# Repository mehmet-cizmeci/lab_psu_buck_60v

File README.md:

# Lab güç kaynağı buck modülü — 0,8–60 V / 0–10 A

TL494 denetleyicili, IR2101 üst kapı sürücülü, asenkron (diyotlu) **buck** dönüştürücü kartı.
Laboratuvar güç kaynağının güç katı olarak tasarlandı: ön paneldeki iki pot ile **gerilim (CV)** ve **akım (CC)** ayarlanır.
İki kanallı bir kaynak için aynı karttan iki adet kullanılabilir.

| | |
|---|---|
| Giriş | 12–70 V DC (60 V çıkış için giriş ≥ 68 V) |
| Çıkış | 0,8–60 V (CV), 0–10 A (CC); en fazla ≈ 300 W |
| Yardımcı besleme | harici +12 V (denetleyici, sürücü, fan) ve +5 V (panel ölçeri) |
| Anahtarlama | ≈ 80 kHz, IRF3710 üst anahtar, MBR20200CT serbest diyot |
| Akım ölçme | 10 mΩ şönt + LM2904, IMON çıkışı 0,2 V/A |
| Kart | 120 × 55 mm, **tek katman** (alt yüz bakır), 1,6 mm FR4 |
| Tasarım | KiCad 10 — şema, kart, kütüphaneler, Gerber ve BOM bu depoda |

## Devre
- **Kontrol:** TL494'ün iki hata yükselteci kullanılır: biri gerilim (CV), biri akım (CC) döngüsü. Tek uçlu mod (pin 13 = GND).
- **Kapı sürücü:** IR2101 yalnız üst çıkışıyla (HO) kullanılır; BCP56/BCP53 emitör izleyici tampon kapıyı ≈ 1 A tepe akımla sürer.
- **Bobin (L1):** iki adet KT130-26 toroid nüve üst üste, 26 tur, 2 × 1,0 mm emaye tel paralel (10 A altında ≈ 75 µH; sardıktan sonra ölçün).
- **Korumalar:**
  - giriş sigortası F1 (6,3 A gecikmeli) ve tek yönlü TVS D12: giriş ters bağlanırsa TVS iletir, F1 atar;
  - çıkış sigortası F2 (10 A) ve ters diyot D4: çıkışa ters akü bağlanırsa F2 atar;
  - hızlı aşırı akım kesmesi (≈ 12 A, karşılaştırıcı → DTC), yumuşak başlatma;
  - pot telleri koparsa ayar 0'a düşer (çıkış kapanır);
  - soğutucuya NC termostat girişi (J9).
- Asenkron yapı çıkıştan girişe akım basmaz; akü veya kondansatör bağlı çıkışta güvenlidir.
- Çıkış eksisi (OUT−) şönt üzerinden geçtiği için **şaseye bağlanmaz**; kanallar seri bağlanmaz.

Şemanın PDF'i: [uretim/lab_psu_buck_60v_sema.pdf](uretim/lab_psu_buck_60v_sema.pdf)

## Bağlantılar
| Konnektör | Pinler |
|---|---|
| J3 GİRİŞ 12–70 V | 1 = +, 2 = GND |
| J2 ÇIKIŞ 0–60 V | 1 = +, 2 = − |
| J1 yardımcı besleme | 1 = GND, 2 = +5 V, 3 = +12 V |
| J7 V POT, J8 I POT | 10 kΩ lineer pot; 3 ve 4 numaralı pinler pot GND ucuna **ayrı tellerle** (kopma algılama) |
| J9 TERMOSTAT | NC termostat (70 °C); kullanılmıyorsa köprüleyin |
| J10 IMON | 0,2 V/A akım çıkışı (panel ölçeri veya mikrodenetleyici) |
| J11 METRE | panel volt/ampermetresi: 1 = +5 V, 2 = ÇIKIŞ−, 3 = ÇIKIŞ+ |
| J12 FAN | 12 V fan |

## Kart ve montaj

- Bakır yalnız **alt yüzde**; evde (toner/lazer) veya tek katman sipariş olarak üretilebilir. SMD parçalar alt yüzde, THT parçalar üst yüzde.
- Üst yüzdeki (F.Cu) yollar ve vialar **tel atlamalarını** gösterir; Gerber'e F.Cu basılmaz:
  - 5 kalın GND teli (1,5 mm delik): ≈ 17, 22, 27, 26 ve 7 mm,
  - 4 ince sinyal teli (0,5 mm delik): SW ≈ 10 mm, VPOT_K ≈ 12 mm, DTC ≈ 20 mm, FB ≈ 12 mm.
- 0 Ω köprüler (R1, R37–R39 1206; R20, R21, R41 2512) SMD bölgesindeki yol geçişleridir.
- Q1 (IRF3710) ve D2 (MBR20200CT) kartın **altında yatık** durur; bacaklar 90° bükülür, sekmeler silikon ped + plastik burçla
  kart boyutundaki alüminyum plakaya bağlanır (sekmeler farklı potansiyelde, mutlaka izole edin). Plakanın üstüne SMD bölgesi için yalıtkan levha koyun.
- Güç yollarının maskesi açıktır; lehim ve bakır telle takviye edilebilir.

## Üretim dosyaları (`uretim/`)
| Dosya | İçerik |
|---|---|
| `lab_psu_buck_60v_gerber.zip` | Gerber (B.Cu, B.Mask, B.Paste, F/B.Silkscreen, Edge.Cuts) + delik dosyası |
| `gerber/` | aynı dosyalar açık hâlde |
| `BOM.csv` | malzeme listesi: üretici parça numarası, **Özdisan** ve **LCSC** stok kodları (`;` ayraçlı) |
| `BOM_JLCPCB.csv`, `CPL_JLCPCB.csv` | montajlı sipariş için LCSC kodlu BOM ve parça konum dosyası |
| `konum_alt_kicad.csv` | KiCad konum dosyası (alt yüz SMD) |
| `lab_psu_buck_60v_sema.pdf` | şema |

Stok kodları örnek olarak verilmiştir (Kasım 2026); sipariş öncesi stok ve fiyatı tedarikçiden kontrol edin.
Bazı Özdisan kodları stok durumuna göre seçilmiş **eşdeğer/muadil** parçalardır, `BOM.csv` "Not" sütununda belirtilmiştir:
- 1 µF 100 V kondansatörler (C5, C6, C7, C12, C13, C14, C33) için 0805 kılıf muadil: 1206 pedine ortalanarak lehimlenir.
- D12 için SMCJ100A (tek yönlü, aynı SMC kılıf). SMCJ85A bulunabiliyorsa o tercih edilir.
- 5×20 cam sigortaların **DC** anma değerini (≥ 80 V DC) veri sayfasından kontrol edin.

**Örnek maliyet (Kasım 2026, KDV ve kargo hariç):** kart üzerindeki malzemeler 1 kart için ≈ 12 USD,
10 kartlık alımda kart başına ≈ 8 USD. PCB, soğutucu, pot, panel ölçeri ve kasa hariçtir.

## KiCad
- KiCad 10 ile `lab_psu_buck_60v.kicad_pro` dosyasını açın.
- Karta özel semboller, footprint'ler ve 3D modeller `kutuphane/` altındadır (`lab_buck`); proje kütüphane tablosu bunları otomatik bulur.
  Diğer parçalar KiCad'in standart kütüphanelerindendir.
- Tasarım kuralları `lab_psu_buck_60v.kicad_dru` içindedir (hat ≥ 0,5 mm, dolgu–yol 1 mm, üst yüzde dolgu yok).
- DRC 0, ERC 0, şema–kart uyumu tam (Rev 0.4).

## İlk çalıştırma ve uyarılar
- Kartta **70 V DC'ye kadar** gerilim ve yüksek akım vardır. İlk denemeyi akım sınırlı bir kaynakla, düşük giriş geriliminde yapın.
- Önce yardımcı beslemeyi (+12 V) verip TL494 osilatörünü ve kapı sinyalini kontrol edin, sonra ana girişi yavaşça yükseltin.
- Kompanzasyon değerleri başlangıç değerleridir; tezgâhta yük basamağı ile doğrulanmalıdır. L1 endüktansını DC öngerilim altında ölçün.
- Q1 ve D2 soğutucusuz çalıştırılmamalıdır.

## Sürüm
**Rev 0.4** (Kasım 2026)

## Lisans
Bu donanım tasarımı **CERN Open Hardware Licence Version 2 – Permissive (CERN-OHL-P v2)** ile lisanslanmıştır, bkz. [LICENSE](LICENSE).

İzan Mekatronik — https://www.izanmekatronik.com.tr

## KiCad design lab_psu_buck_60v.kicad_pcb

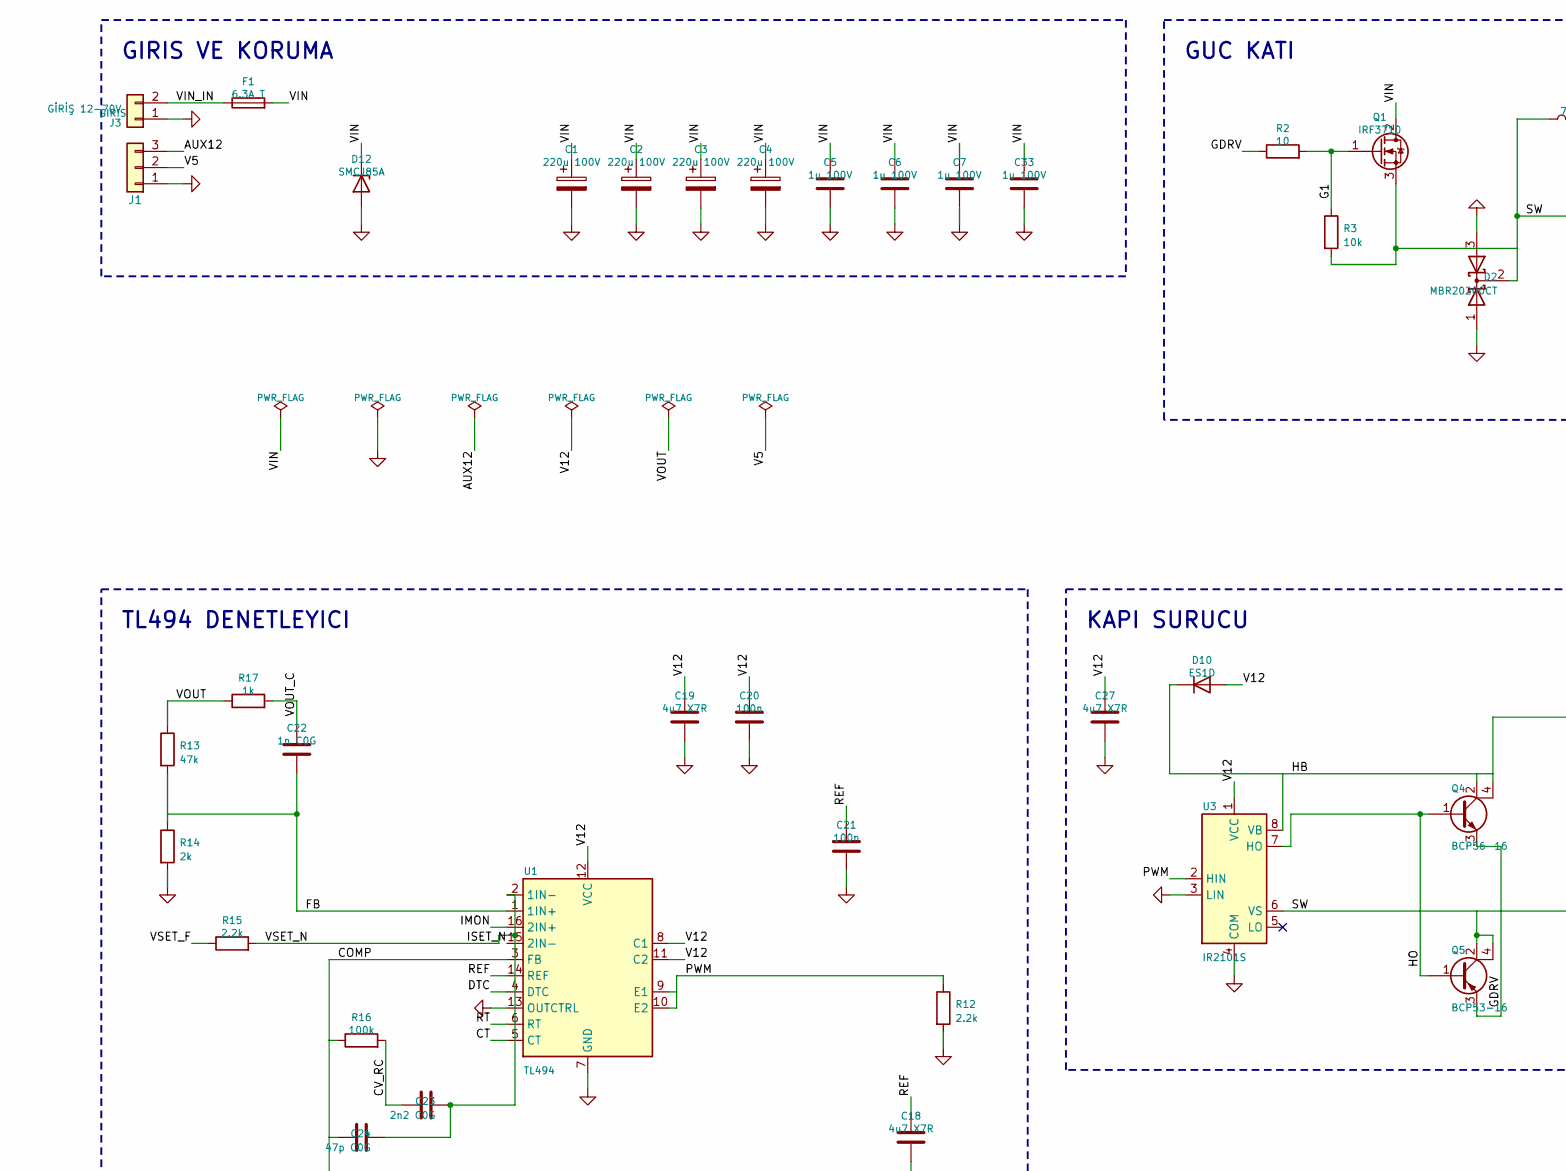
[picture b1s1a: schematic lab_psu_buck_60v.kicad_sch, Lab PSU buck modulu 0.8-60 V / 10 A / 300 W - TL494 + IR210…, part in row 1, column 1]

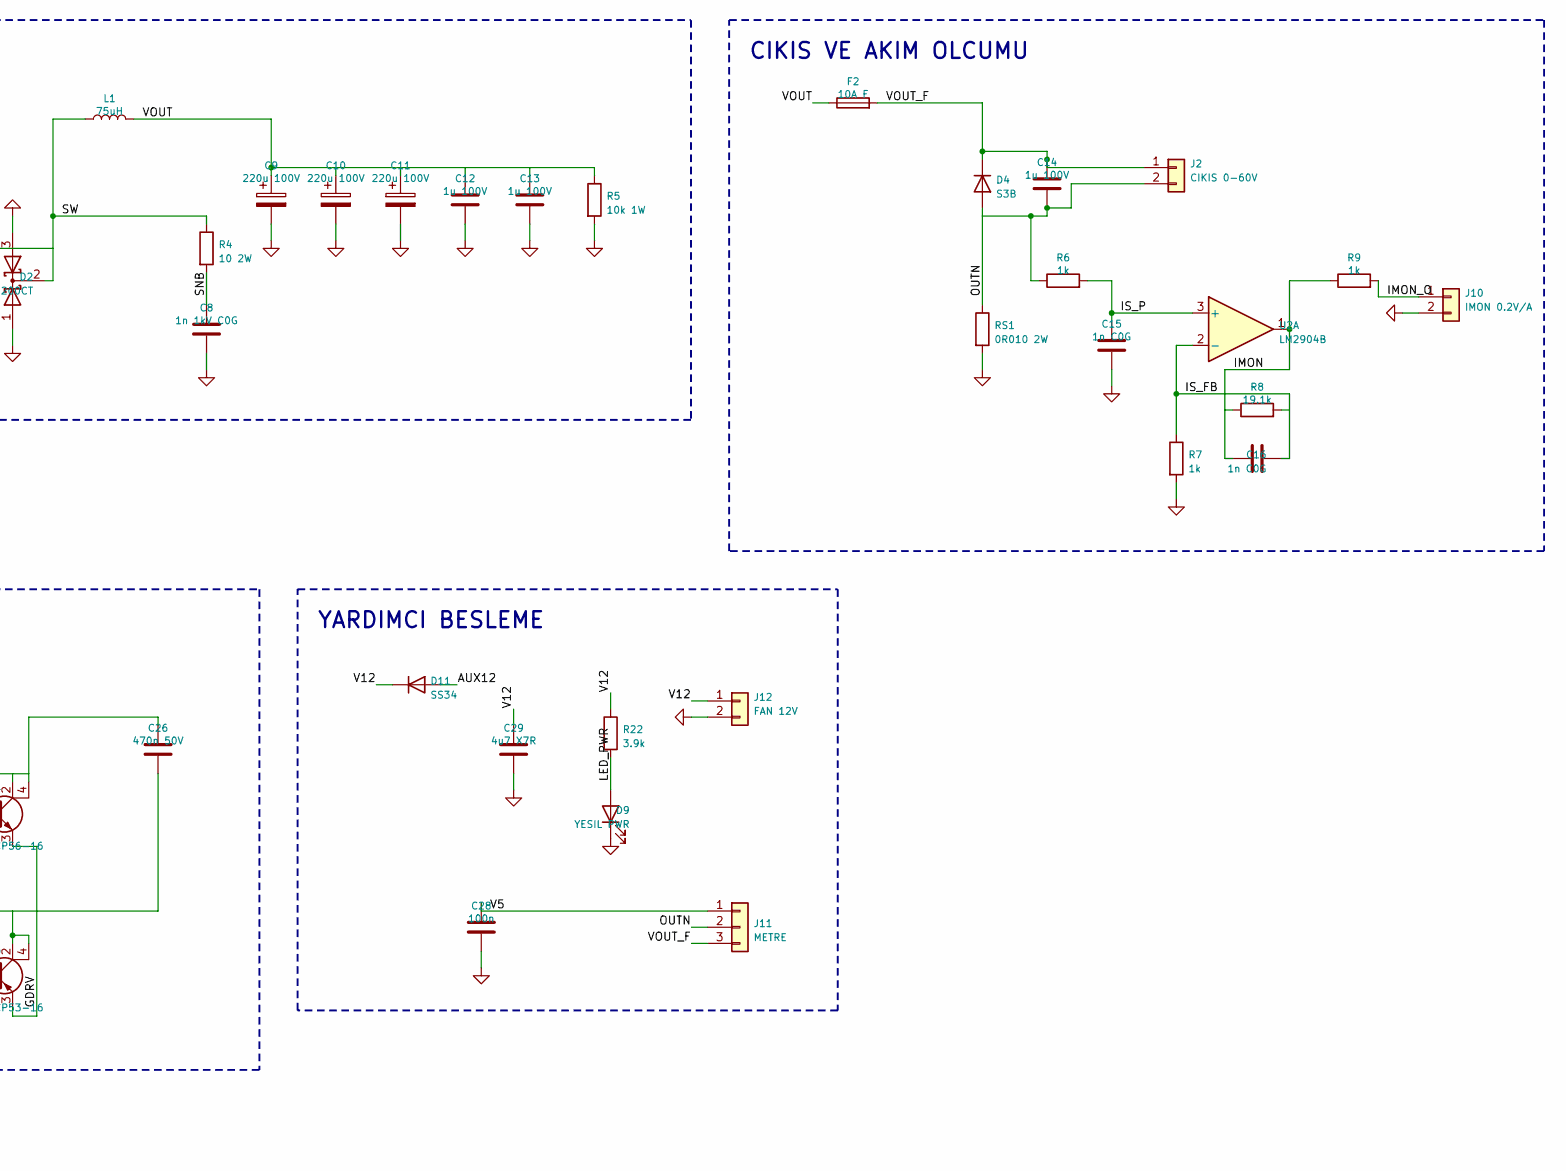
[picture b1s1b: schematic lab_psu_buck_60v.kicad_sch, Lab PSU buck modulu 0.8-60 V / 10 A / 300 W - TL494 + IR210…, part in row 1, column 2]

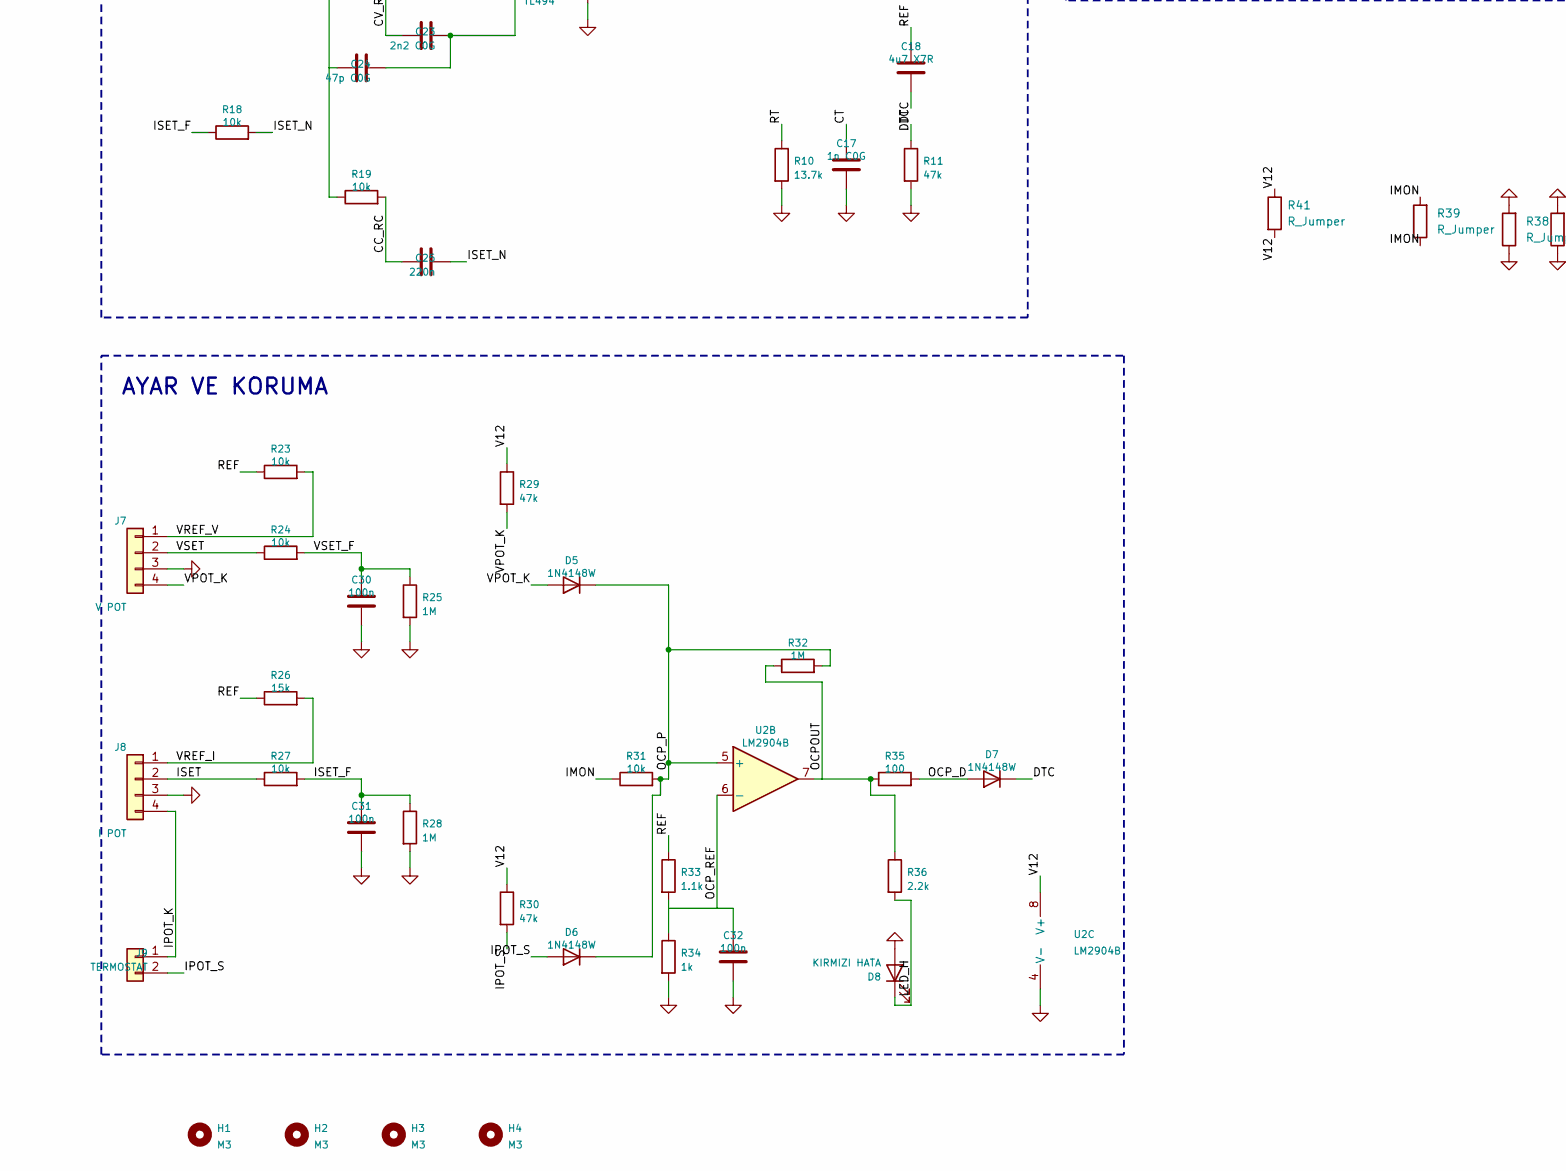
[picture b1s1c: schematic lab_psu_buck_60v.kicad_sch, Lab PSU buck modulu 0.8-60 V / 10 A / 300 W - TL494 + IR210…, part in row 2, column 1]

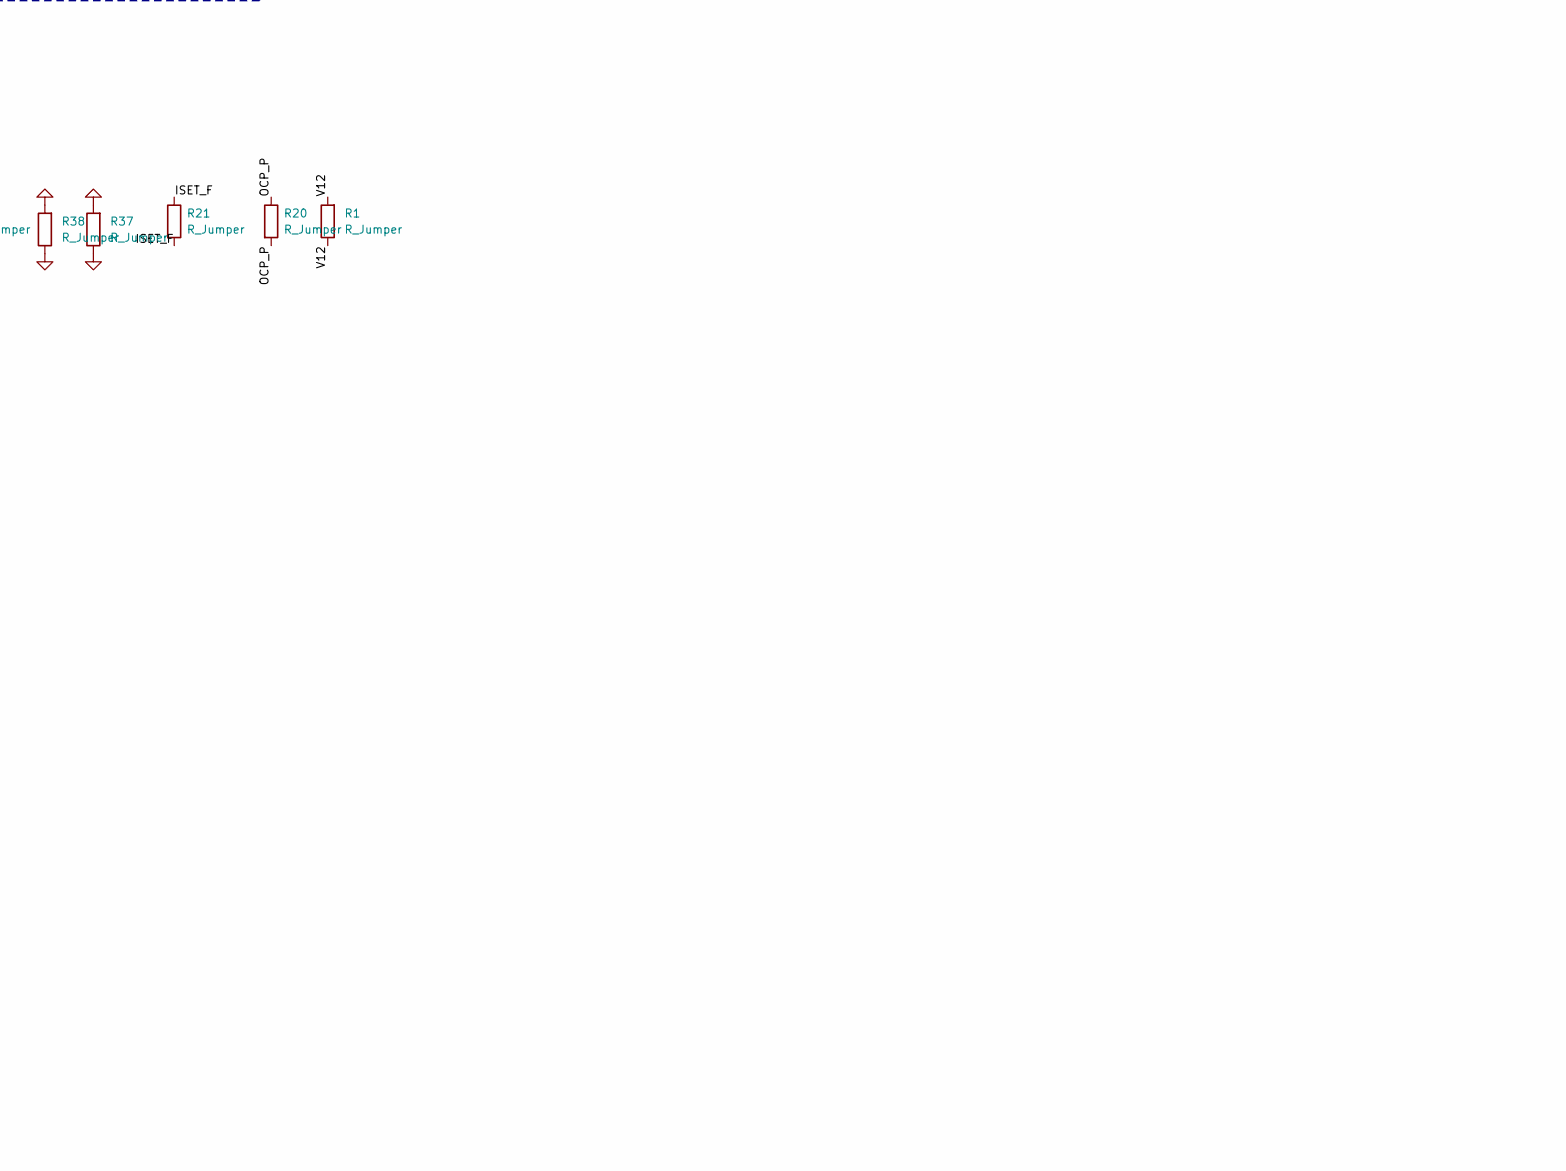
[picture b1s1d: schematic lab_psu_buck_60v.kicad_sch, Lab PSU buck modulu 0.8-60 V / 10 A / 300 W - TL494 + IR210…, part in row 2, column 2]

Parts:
C1, C2, C3, C4, C9, C10, C11: 220u 100V; CP_Radial_D12.5mm_P5.00mm; MPN PKLH-100V221MH250-T/A5.0
C5, C6, C7, C12, C13, C14, C33: 1u 100V; C_1206_3216Metric; MPN CL31B105KCHNNNE
C8: 1n 1kV C0G; C_1206_3216Metric; MPN MCF06JTN102102
C15, C16, C17, C22: 1n C0G; C_0603_1608Metric_Pad1.08x0.95mm_HandSolder; MPN CC0603JRNPO9BN102
C18, C19, C27, C29: 4u7 X7R; C_1206_3216Metric; MPN CL31B475KBHNNNE
C20, C21, C28, C30, C31, C32: 100n; C_0603_1608Metric_Pad1.08x0.95mm_HandSolder; MPN CC0603KRX7R9BB104
C23: 2n2 C0G; C_0603_1608Metric_Pad1.08x0.95mm_HandSolder; MPN CL10C222JB8NNNC
C24: 47p C0G; C_0603_1608Metric_Pad1.08x0.95mm_HandSolder; MPN CL10C470JB8NNNC
C25: 220n; C_0603_1608Metric_Pad1.08x0.95mm_HandSolder; MPN CL10B224KA8NNNC
C26: 470n 50V; C_1206_3216Metric; MPN CL31B474KBHNNNE
D2: MBR20200CT; TO-220-3_Horizontal_TabUp_Ters6mm; MPN MBR20200CT_T0_00001
D4: S3B; D_SMC; MPN S3B_R2_00001
D5, D6, D7: 1N4148W; D_SOD-123; MPN 1N4148W-HT
D8: KIRMIZI HATA; LED_D3.0mm; MPN 3R4UD-8
D9: YESIL PWR; LED_D3.0mm; MPN 3G4HD-G03-CT
D10: ES1D; D_SMA_Handsoldering; MPN ES1D
D11: SS34; D_SMA_Handsoldering; MPN SS34
D12: SMCJ85A; D_SMC; MPN SMCJ85A
F1: 6.3A T; Fuseholder_Clip-5x20mm_Keystone_3517_Inline_P23.11x6.76mm_D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
F2: 10A F; Fuseholder_Clip-5x20mm_Keystone_3517_Inline_P23.11x6.76mm_D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
H1, H2, H3, H4: M3; MountingHole_3.2mm_M3
J1: GIRIS; TerminalBlock_Phoenix_MKDS-1,5-3-5.08_1x03_P5.08mm_Horizont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; MPN DG128-5.0-03P-14-00AH
J2: CIKIS 0-60V; TerminalBlock_Degson_DG950_1x02_P9.50mm; MPN DG950-9.5-02P-14-00AH
J3: GİRİŞ 12-70V; TerminalBlock_Degson_DG950_1x02_P9.50mm; MPN DG950-9.5-02P-14-00AH
J7: V POT; PinHeader_1x04_P2.54mm_Vertical; MPN L-KLS1-207-1-40-S-3X13.5
J8: I POT; PinHeader_1x04_P2.54mm_Vertical; MPN L-KLS1-207-1-40-S-3X13.5
J9: TERMOSTAT; PinHeader_1x02_P2.54mm_Vertical; MPN L-KLS1-207-1-40-S-3X13.5
J10: IMON 0.2V/A; PinHeader_1x02_P2.54mm_Vertical; MPN L-KLS1-207-1-40-S-3X13.5
J11: METRE; PinHeader_1x03_P2.54mm_Vertical; MPN L-KLS1-207-1-40-S-3X13.5
J12: FAN 12V; PinHeader_1x02_P2.54mm_Vertical; MPN L-KLS1-207-1-40-S-3X13.5
L1: 75uH; Toroid_D36_Yatay; MPN KT130-26A
Q1: IRF3710; TO-220-3_Horizontal_TabUp_Ters6mm; MPN IRF3710PBF
Q4: BCP56-16; SOT-223-3_TabPin2_Pin4; MPN BCP56-16-AU_R2_007A1
Q5: BCP53-16; SOT-223-3_TabPin2_Pin4; MPN BCP53-16,135-HT
R1, R37, R38, R39: R_Jumper; R_1206_0R_Kopru_HandSolder
R2: 10; R_1206_3216Metric; MPN 1206S4F100JT5E
R3, R18, R19, R23, R24, R27, R31: 10k; R_0603_1608Metric_Pad0.98x0.95mm_HandSolder; MPN 0603SAJ0103T5E
R4: 10 2W; R_2512_6332Metric; MPN AS122WK0100T4E
R5: 10k 1W; R_2512_6332Metric; MPN RC2512JK-0710KL
R6, R9, R34: 1k; R_0603_1608Metric_Pad0.98x0.95mm_HandSolder; MPN 0603SAJ0102T5E
R7, R17: 1k; R_1206_3216Metric; MPN 1206S4F1001T5E
R8: 19.1k; R_0603_1608Metric_Pad0.98x0.95mm_HandSolder; MPN 0603SAF1912T5E
R10: 13.7k; R_0603_1608Metric_Pad0.98x0.95mm_HandSolder; MPN 0603SAF1372T5E
R11, R29, R30: 47k; R_0603_1608Metric_Pad0.98x0.95mm_HandSolder; MPN 0603SAJ0473T5E
R12, R15, R36: 2.2k; R_0603_1608Metric_Pad0.98x0.95mm_HandSolder; MPN 0603SAF2201T5E
R13: 47k; R_1206_3216Metric; MPN 1206S4F4702T5E
R14: 2k; R_1206_3216Metric; MPN 1206S4F2001T5E
R16: 100k; R_0603_1608Metric_Pad0.98x0.95mm_HandSolder; MPN 0603SAF1003T5E
R20, R21, R41: R_Jumper; R_2512_0R_Kopru
R22: 3.9k; R_0603_1608Metric_Pad0.98x0.95mm_HandSolder; MPN 0603SAF3901T5E
R25, R28, R32: 1M; R_0603_1608Metric_Pad0.98x0.95mm_HandSolder; MPN RC0603FR-071ML
R26: 15k; R_0603_1608Metric_Pad0.98x0.95mm_HandSolder; MPN 0603SAF1502T5E
R33: 1.1k; R_0603_1608Metric_Pad0.98x0.95mm_HandSolder; MPN 0603SAF1101T5E
R35: 100; R_0603_1608Metric_Pad0.98x0.95mm_HandSolder; MPN 0603SAJ0101T5E
RS1: 0R010 2W; R_2512_6332Metric; MPN PE2512DKE7W0R01L
U1: TL494; SOIC-16_3.9x9.9mm_P1.27mm; MPN TL494G-S16-R
U2: LM2904B; SOIC-8_3.9x4.9mm_P1.27mm; MPN LM2904BIDR
U3: IR2101S; SOIC-8_3.9x4.9mm_P1.27mm; MPN IR2101STRPBF

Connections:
/AUX12: D11.2 (A), J1.3
/CC_RC: C25.1, R19.2
/COMP: C24.1, R16.1, R19.1, U1.3 (FB)
/CT: C17.1, U1.5 (CT)
/CV_RC: C23.1, R16.2
/DTC: C18.2, D7.1 (K), R11.1, U1.4 (DTC)
/FB: C22.2, R13.2, R14.1, U1.1 (1IN+)
/G1: Q1.1 (G), R2.2, R3.1
/GDRV: Q4.3 (E), Q5.3 (E), R2.1
/HB: C26.1, D10.1 (K), Q4.2 (C), Q4.4 (C), U3.8 (VB)
/HO: Q4.1 (B), Q5.1 (B), U3.7 (HO)
/IMON: C16.1, R8.1, R9.1, R31.1, R39.1, R39.2, U1.16 (2IN+), U2.1
/IMON_O: J10.1, R9.2
/IPOT_K: J8.4, J9.1
/IPOT_S: D6.2 (A), J9.2, R30.2
/ISET: J8.2, R27.1
/ISET_F: C31.1, R18.1, R21.1, R21.2, R27.2, R28.1
/ISET_N: C25.2, R18.2, U1.15 (2IN-)
/IS_FB: C16.2, R7.1, R8.2, U2.2 (-)
/IS_P: C15.1, R6.2, U2.3 (+)
/LED_H: D8.1 (K), R36.2
/LED_PWR: D9.2 (A), R22.2
/OCPOUT: R32.1, R35.1, R36.1, U2.7
/OCP_D: D7.2 (A), R35.2
/OCP_P: D5.1 (K), D6.1 (K), R20.1, R20.2, R31.2, R32.2, U2.5 (+)
/OCP_REF: C32.1, R33.2, R34.1, U2.6 (-)
/OUTN: C14.2, D4.2 (A), J2.2, J11.2, R6.1, RS1.1
/PWM: R12.1, U1.9 (E1), U1.10 (E2), U3.2 (HIN)
/REF: C18.1, C21.1, R23.1, R26.1, R33.1, U1.14 (REF)
/RT: R10.1, U1.6 (RT)
/SNB: C8.1, R4.2
/SW: C26.2, D2.2 (K), L1.1, Q1.3 (S), Q5.2 (C), Q5.4 (C), R3.2, R4.1, U3.6 (VS)
/V5: C28.1, J1.2, J11.1
/V12: C19.1, C20.1, C27.1, C29.1, D10.2 (A), D11.1 (K), J12.1, R1.1, R1.2, R22.1, R29.1, R30.1, R41.1, R41.2, U1.8 (C1), U1.11 (C2), U1.12 (VCC), U2.8 (V+), U3.1 (VCC)
/VIN: C1.1, C2.1, C3.1, C4.1, C5.1, C6.1, C7.1, C33.1, D12.1 (K), F1.2, Q1.2 (D)
/VIN_IN: F1.1, J3.2
/VOUT: C9.1, C10.1, C11.1, C12.1, C13.1, F2.1, L1.2, R5.1, R13.1, R17.1
/VOUT_C: C22.1, R17.2
/VOUT_F: C14.1, D4.1 (K), F2.2, J2.1, J11.3
/VPOT_K: D5.2 (A), J7.4, R29.2
/VREF_I: J8.1, R26.2
/VREF_V: J7.1, R23.2
/VSET: J7.2, R24.1
/VSET_F: C30.1, R15.1, R24.2, R25.1
/VSET_N: C23.2, C24.2, R15.2, U1.2 (1IN-)
GND: C1.2, C2.2, C3.2, C4.2, C5.2, C6.2, C7.2, C8.2, C9.2, C10.2, C11.2, C12.2, C13.2, C15.2, C17.2, C19.2, C20.2, C21.2, C27.2, C28.2, C29.2, C30.2, C31.2, C32.2, C33.2, D2.1 (A), D2.3 (A), D8.2 (A), D9.1 (K), D12.2 (A), J1.1, J3.1, J7.3, J8.3, J10.2, J12.2, R5.2, R7.2, R10.2, R11.2, R12.2, R14.2, R25.2, R28.2, R34.2, R37.1, R37.2, R38.1, R38.2, RS1.2, U1.7 (GND), U1.13 (OUTCTRL), U2.4 (V-), U3.3 (LIN), U3.4 (COM)

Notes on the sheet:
GUC KATI
AYAR VE KORUMA
CIKIS VE AKIM OLCUMU
YARDIMCI BESLEME
TL494 DENETLEYICI
GIRIS VE KORUMA
KAPI SURUCU

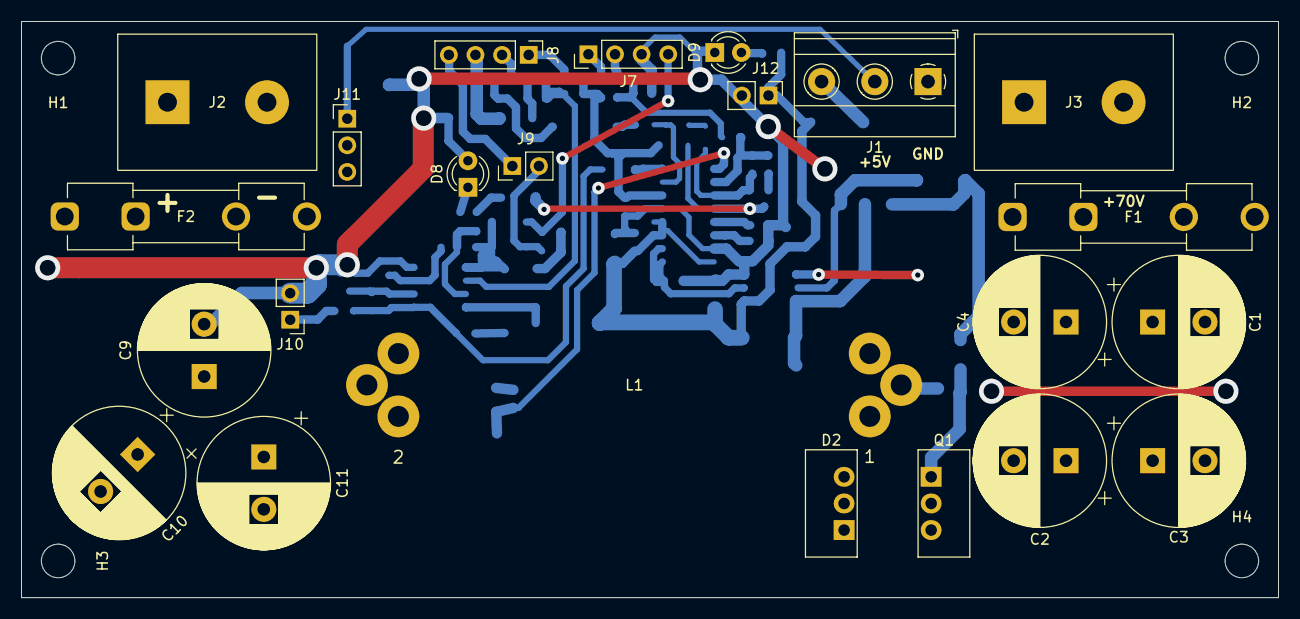
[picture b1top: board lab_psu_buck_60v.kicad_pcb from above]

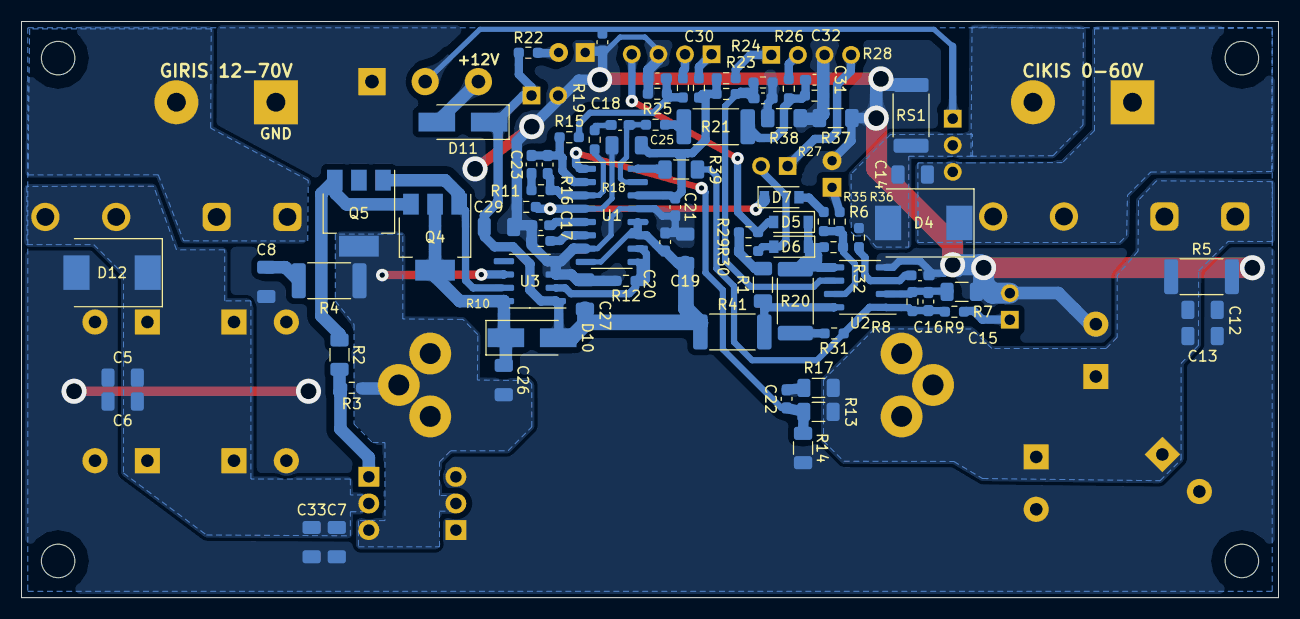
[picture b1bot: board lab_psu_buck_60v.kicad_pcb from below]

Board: 2 copper layers, 120.0 x 55.0 mm, 106 parts (79 on the bottom side), 46 nets.

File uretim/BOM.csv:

Adet;Referanslar;Deger;Kilif;Uretici;Parca no (MPN);Ozdisan stok kodu;LCSC kodu;Not
6;C20, C21, C28, C30, C31, C32;100n;C_0603_1608Metric_Pad1.08x0.95mm_HandSolder;YAGEO;CC0603KRX7R9BB104;CC0603KRX7R9BB104;C14663;
1;C8;1n 1kV C0G;C_1206_3216Metric;VIKING;MCF06JTN102102;MCF06JTN102102;C113872;snubber, degeri tezgahta ayarlanabilir
4;C15, C16, C17, C22;1n C0G;C_0603_1608Metric_Pad1.08x0.95mm_HandSolder;YAGEO;CC0603JRNPO9BN102;CC0603JRNPO9BN102;C106246;
7;C5, C6, C7, C12, C13, C14, C33;1u 100V;C_1206_3216Metric;SAMSUNG;CL31B105KCHNNNE;CL21Y105KCFVPJE;C13832;"1206 100 V; Ozdisan kodu 0805 muadildir, 1206 pedine ortalanarak lehimlenir"
1;C25;220n;C_0603_1608Metric_Pad1.08x0.95mm_HandSolder;SAMSUNG;CL10B224KA8NNNC;CL10B224KA8NNNC;C21120;
7;C1, C2, C3, C4, C9, C10, C11;220u 100V;CP_Radial_D12.5mm_P5.00mm;KOSHIN;PKLH-100V221MH250-T/A5.0;PKLH-100V221MH250-T/A5.0;C5213780;giris/cikis elektrolitik, 100 V sart (giris 70 V)
1;C23;2n2 C0G;C_0603_1608Metric_Pad1.08x0.95mm_HandSolder;SAMSUNG;CL10C222JB8NNNC;CL10C222JB8NNNC;C33353;
1;C26;470n 50V;C_1206_3216Metric;SAMSUNG;CL31B474KBHNNNE;CL31B474KBHNNNE;C71084;bootstrap
1;C24;47p C0G;C_0603_1608Metric_Pad1.08x0.95mm_HandSolder;SAMSUNG;CL10C470JB8NNNC;CL10C470JB8NNNC;C1671;
4;C18, C19, C27, C29;4u7 X7R;C_1206_3216Metric;SAMSUNG;CL31B475KBHNNNE;CL31B475KBHNNNE;C51205;yumusak baslama
3;D5, D6, D7;1N4148W;D_SOD-123;HOTTECH;1N4148W-HT;1N4148W-HT;C81598;pot kopma korumasi
1;D10;ES1D;D_SMA_Handsoldering;;ES1D;ES1D-SMA;C84602;bootstrap diyotu (200 V hizli). Ozdisan kodu esdegerdir
1;D8;KIRMIZI HATA;LED_D3.0mm;STRONG BASE;3R4UD-8;3R4UD-8;C779429;
1;D2;MBR20200CT;TO-220-3_Horizontal_TabUp_Ters6mm;PANJIT;MBR20200CT_T0_00001;MBR20200CT_T0_00001;C2727;"serbest diyot, iki kol paralel; sogutucuya izoleli"
1;D4;S3B;D_SMC;PANJIT;S3B_R2_00001;S3B_R2_00001;C3035888;cikista ters aku korumasi (F2 atar)
1;D12;SMCJ85A;D_SMC;LITTELFUSE;SMCJ85A;SMCJ100A-TKS;C438123;"giris TVS, tek yonlu; ters baglantida iletir, F1 atar. Ozdisan kodu SMCJ100A muadildir"
1;D11;SS34;D_SMA_Handsoldering;;SS34;SS34-MD;C8678;harici 12 V ters baglanti korumasi. Ozdisan kodu esdegerdir
1;D9;YESIL PWR;LED_D3.0mm;CHINA TOTAL;3G4HD-G03-CT;3G4HD-G03-CT;;
1;F2;10A F;Fuseholder_Clip-5x20mm_Keystone_3517_Inline_P23.11x6.76mm_D1.70mm_Horizontal;;;5GT10A;;"cikis 10 A hizli; 5x20 sigorta klipsi"
1;F1;6.3A T;Fuseholder_Clip-5x20mm_Keystone_3517_Inline_P23.11x6.76mm_D1.70mm_Horizontal;;;TBC1630A;;"giris 6,3 A gecikmeli; 5x20 sigorta klipsi"
1;J2;CIKIS 0-60V;TerminalBlock_Degson_DG950_1x02_P9.50mm;DEGSON;DG950-9.5-02P-14-00AH;DG950-9.5-02P-14-00AH;;CIKIS: 1=+ 2=- (cikis eksisi sasiye baglanmaz)
1;J12;FAN 12V;PinHeader_1x02_P2.54mm_Vertical;KLS;L-KLS1-207-1-40-S-3X13.5;L-KLS1-207-1-40-S-3X13.5;C2337;fan 12 V
1;J1;GIRIS;TerminalBlock_Phoenix_MKDS-1,5-3-5.08_1x03_P5.08mm_Horizontal;DEGSON;DG128-5.0-03P-14-00AH;DG128-5.0-03P-14-00AH;C691861;yardimci besleme: 1=GND 2=+5V 3=+12V
1;J3;GİRİŞ 12-70V;TerminalBlock_Degson_DG950_1x02_P9.50mm;DEGSON;DG950-9.5-02P-14-00AH;DG950-9.5-02P-14-00AH;;GIRIS 12-70 V DC: 1=+ 2=GND
1;J8;I POT;PinHeader_1x04_P2.54mm_Vertical;KLS;L-KLS1-207-1-40-S-3X13.5;L-KLS1-207-1-40-S-3X13.5;C2337;"I POT, 10k lineer; 3 ve 4 pot GND ucuna ayri tellerle"
1;J10;IMON 0.2V/A;PinHeader_1x02_P2.54mm_Vertical;KLS;L-KLS1-207-1-40-S-3X13.5;L-KLS1-207-1-40-S-3X13.5;C2337;IMON 0,2 V/A (panel ampermetresi / MCU)
1;J11;METRE;PinHeader_1x03_P2.54mm_Vertical;KLS;L-KLS1-207-1-40-S-3X13.5;L-KLS1-207-1-40-S-3X13.5;C2337;panel volt/ampermetre: 1=+5V 2=CIKIS- 3=CIKIS+
1;J9;TERMOSTAT;PinHeader_1x02_P2.54mm_Vertical;KLS;L-KLS1-207-1-40-S-3X13.5;L-KLS1-207-1-40-S-3X13.5;C2337;"NC termostat (70 C) sogutucuya; kullanilmazsa jumper"
1;J7;V POT;PinHeader_1x04_P2.54mm_Vertical;KLS;L-KLS1-207-1-40-S-3X13.5;L-KLS1-207-1-40-S-3X13.5;C2337;"V POT, 10k lineer; 3 ve 4 pot GND ucuna ayri tellerle"
2;L1;75uH;Toroid_D36_Yatay;FUANTRONICS;KT130-26A;KT130-26A;;2 nuve ust uste, 26 tur 2x1,0 mm emaye paralel (~75 uH @10 A, olculmeli)
1;Q5;BCP53-16;SOT-223-3_TabPin2_Pin4;HOTTECH;BCP53-16,135-HT;BCP53-16,135-HT;C82081;kapi tamponu (emitor izleyici)
1;Q4;BCP56-16;SOT-223-3_TabPin2_Pin4;PANJIT;BCP56-16-AU_R2_007A1;BCP56-16-AU_R2_007A1;C16602;kapi tamponu (emitor izleyici)
1;Q1;IRF3710;TO-220-3_Horizontal_TabUp_Ters6mm;INFINEON;IRF3710PBF;IRF3710PBF;C2562;ust anahtar, izoleli ped + burc ile sogutucuya
1;R33;1.1k;R_0603_1608Metric_Pad0.98x0.95mm_HandSolder;ROYALOHM;0603SAF1101T5E;0603SAF1101T5E;C22764;
1;R2;10;R_1206_3216Metric;ROYALOHM;1206S4F100JT5E;1206S4F100JT5E;C17903;
1;R4;10 2W;R_2512_6332Metric;ROYALOHM;AS122WK0100T4E;AS122WK0100T4E;C5123624;snubber direnci
1;R35;100;R_0603_1608Metric_Pad0.98x0.95mm_HandSolder;ROYALOHM;0603SAJ0101T5E;0603SAJ0101T5E;C22775;
1;R16;100k;R_0603_1608Metric_Pad0.98x0.95mm_HandSolder;ROYALOHM;0603SAF1003T5E;0603SAF1003T5E;C25803;
7;R3, R18, R19, R23, R24, R27, R31;10k;R_0603_1608Metric_Pad0.98x0.95mm_HandSolder;ROYALOHM;0603SAJ0103T5E;0603SAJ0103T5E;C25804;
1;R5;10k 1W;R_2512_6332Metric;YAGEO;RC2512JK-0710KL;RC2512JK-0710KL;C137016;bosaltma direnci
1;R10;13.7k;R_0603_1608Metric_Pad0.98x0.95mm_HandSolder;ROYALOHM;0603SAF1372T5E;0603SAF1372T5E;C22793;
1;R26;15k;R_0603_1608Metric_Pad0.98x0.95mm_HandSolder;ROYALOHM;0603SAF1502T5E;0603SAF1502T5E;C22809;
1;R8;19.1k;R_0603_1608Metric_Pad0.98x0.95mm_HandSolder;ROYALOHM;0603SAF1912T5E;0603SAF1912T5E;C22897;
3;R25, R28, R32;1M;R_0603_1608Metric_Pad0.98x0.95mm_HandSolder;YAGEO;RC0603FR-071ML;RC0603FR-071ML;C22935;
2;R7, R17;1k;R_1206_3216Metric;ROYALOHM;1206S4F1001T5E;1206S4F1001T5E;C4410;
3;R6, R9, R34;1k;R_0603_1608Metric_Pad0.98x0.95mm_HandSolder;ROYALOHM;0603SAJ0102T5E;0603SAJ0102T5E;C21190;
3;R12, R15, R36;2.2k;R_0603_1608Metric_Pad0.98x0.95mm_HandSolder;ROYALOHM;0603SAF2201T5E;0603SAF2201T5E;C4190;
1;R14;2k;R_1206_3216Metric;ROYALOHM;1206S4F2001T5E;RC1206FR-072KL;C17944;FB alt %1. Ozdisan kodu esdegerdir
1;R22;3.9k;R_0603_1608Metric_Pad0.98x0.95mm_HandSolder;ROYALOHM;0603SAF3901T5E;0603SAF3901T5E;C23018;
3;R11, R29, R30;47k;R_0603_1608Metric_Pad0.98x0.95mm_HandSolder;ROYALOHM;0603SAJ0473T5E;0603SAJ0473T5E;C25819;
1;R13;47k;R_1206_3216Metric;ROYALOHM;1206S4F4702T5E;RC1206FR-0747KL;C25833;FB ust %1. Ozdisan kodu esdegerdir
4;R1, R37, R38, R39;0R;R_1206_0R_Kopru_HandSolder;;;1206S4J0000T5E;C19290;0R kopru (1206)
3;R20, R21, R41;0R;R_2512_0R_Kopru;;;25121WJ0000T4E;C25469;0R kopru (2512)
1;RS1;0R010 2W;R_2512_6332Metric;YAGEO;PE2512DKE7W0R01L;PE2512DKE7W0R01L;C500718;akim sontu %1
1;U3;IR2101S;SOIC-8_3.9x4.9mm_P1.27mm;INFINEON;IR2101STRPBF;IR2101STRPBF;C2683752;yalniz HO kullanilir
1;U2;LM2904B;SOIC-8_3.9x4.9mm_P1.27mm;TEXAS;LM2904BIDR;LM2904BIDR;C476365;akim olcme / asiri akim
1;U1;TL494;SOIC-16_3.9x9.9mm_P1.27mm;UTC;TL494G-S16-R;TL494G-S16-R;C5274811;PWM denetleyici, tek uclu mod

Ek / kart disi malzemeler
1 (40 pin serit, 2 karta yeter);J7-J12;pin header 2,54 mm;;KLS;L-KLS1-207-1-40-S-3X13.5;L-KLS1-207-1-40-S-3X13.5;C2337;17 pin/kart
1;F1;sigorta 6,3 A T 5x20;;;;TBC1630A;;DC anma degerini (>= 80 V DC) veri sayfasindan teyit edin
1;F2;sigorta 10 A F 5x20;;;;5GT10A;;DC anma degerini (>= 80 V DC) veri sayfasindan teyit edin
4;F1, F2;5x20 sigorta klipsi (Keystone 3517 tipi);;;;;;yerel temin
2;Q1, D2;TO-220 silikon izolasyon pedi;;;;HC-TO220;;
2;Q1, D2;TO-220 plastik burc;;;;L-KLS8-0222-PTO-220A;;
2;J7, J8;10k lineer panel potu;;;;;;kart disi, yerel temin
1;J11;panel volt/ampermetre (DSN-VC288 tipi);;;;;;kart disi, yerel temin
1;J9;NC termostat 70 C (KSD9700 tipi);;;;;;kart disi, yerel temin
~6 m;L1;1,0 mm emaye bakir tel;;;;;;kart disi, yerel temin
1;-;kart boyu aluminyum soguatma plakasi + M3 burc;;;;;;"kart disi; Q1 ve D2 izoleli baglanir"
